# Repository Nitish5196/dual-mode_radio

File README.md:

<h1>DUAL_MODE_RADIO-DMR </h1>
DMR(DUAL MODE RADIO) is a small portable radio that combines two different things in one device:<ul>
<li>AIRLINK is a small portable radio that combines two different things in one device:</li>
<li>VHF amateur radio for two-way communication</li></ul><br>
The controller is an ESP32. It controls the display, buttons, rotary encoder and the radio module<br>
<h3> Main Components</h3>

- ESP32 DevKitC – main controller
- SA828-VHF – VHF transceiver
- RDA5807M – FM receiver
- PAM8403 – audio amplifier
- OLED – displays frequency and status
- Rotary Encoder – tuning and navigation
- TP4056 – battery charging
- Boost Converter – provides 5V power
- 3.3V Regulator – provides 3.3V power
- 18650 – rechargeable battery
- SMA Connector – VHF antenna connection
- Speakers – audio output
<h2>BOM:</h2>
<ul>
<li>Custom PCB ×1</li>
<li>ESP32 DevKitC ×1</li>
<li>SA828-VHF ×1</li>
<li>RDA5807M FM Module ×1</li>
<li>PAM8403 Amplifier Module ×1</li>
<li>0.96" OLED Display ×1</li>
<li>Rotary Encoder ×1</li>
<li>Push Buttons ×3</li>
<li>ON/OFF Switch ×1</li>
<li>RK097G B100K Potentiometer ×1</li>
<li>SMA Connector ×1</li>
<li>TP4056 Charger ×1</li>
<li>5V Boost Converter ×1</li>
<li>3.3V Regulator ×1</li>
<li>18650 Battery ×1</li>
<li>8Ω Speakers ×3</li>
<li>2.54mm Headers/Connectors ×1 set</li>
<li>3D Printed Case ×1</li>
<li>Breadboard ×1</li>
<li>Male-to-Male Jumper Wires ×1 set</li>
<li>Male-to-Female Jumper Wires ×1 set</li>
<li>Female-to-Female Jumper Wires ×1 set</li>
</ul>
<h2>PCB:</h2>

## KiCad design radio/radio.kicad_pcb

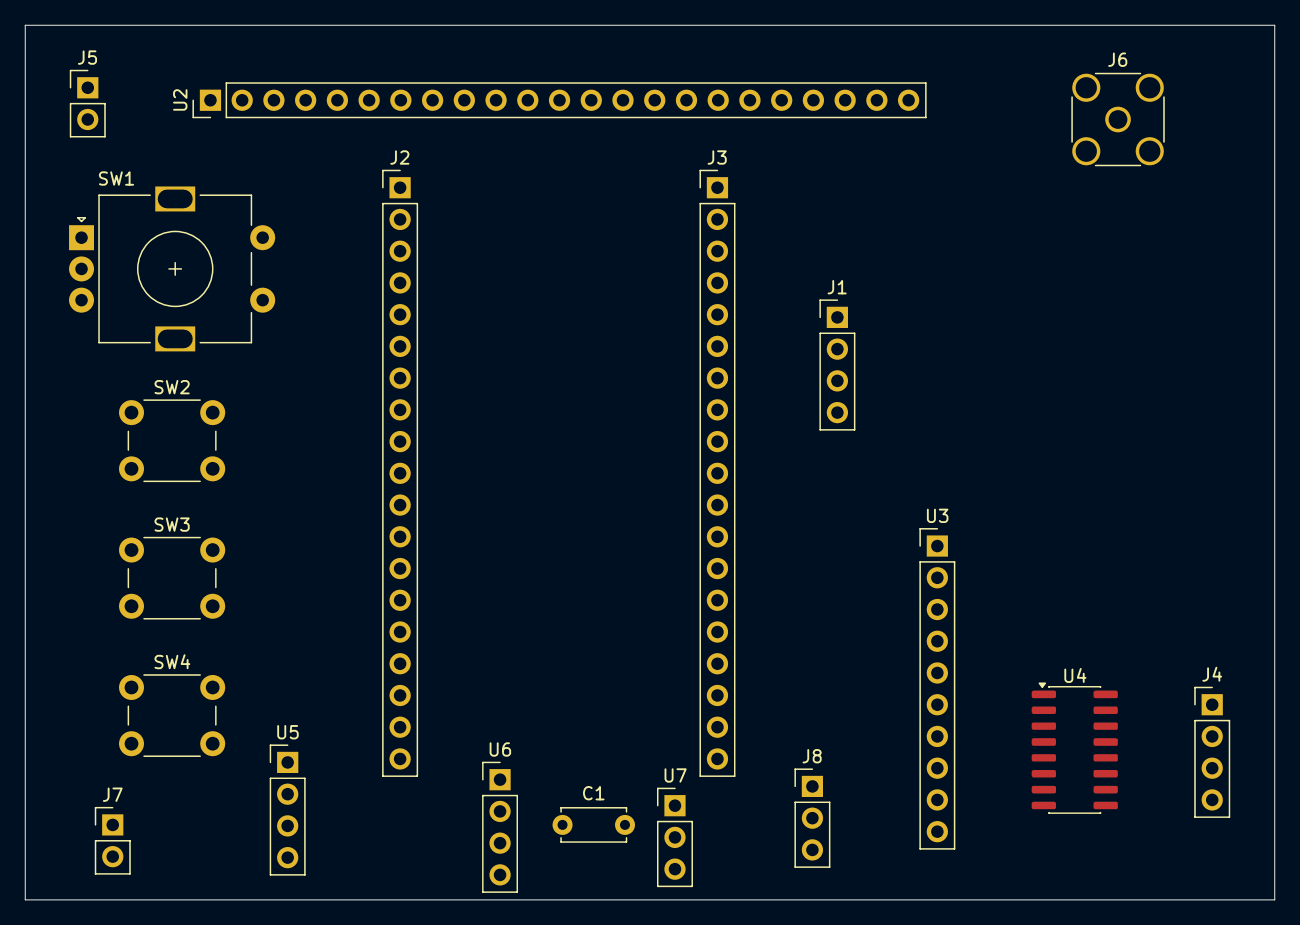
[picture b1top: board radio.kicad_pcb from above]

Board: 2 copper layers, 100.0 x 70.0 mm, 19 parts (0 on the bottom side), 26 nets, no tracks yet.

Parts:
C1: 100nF; C_Disc_D5.0mm_W2.5mm_P5.00mm
J1: Conn_01x04; PinHeader_1x04_P2.54mm_Vertical
J2: ESP32_LEFT; PinHeader_1x19_P2.54mm_Vertical
J3: ESP32_RIGHT; PinHeader_1x19_P2.54mm_Vertical
J4: FM_SPEAKERS; PinHeader_1x04_P2.54mm_Vertical
J5: RADIO_MIC; PinHeader_1x02_P2.54mm_Vertical
J6: ANTENNA_VHF; SMA_Amphenol_132134_Vertical
J7: BATTERY_18650; PinHeader_1x02_P2.54mm_Vertical
J8: POWER_SWITCH; PinHeader_1x03_P2.54mm_Vertical
SW1: ROTARY_ENCODER; RotaryEncoder_Alps_EC11E-Switch_Vertical_H20mm
SW2, SW3, SW4: SW_Push; SW_PUSH_6mm
U2: SA828-VHF; PinHeader_1x23_P2.54mm_Vertical
U3: RDA5807M-FM; PinHeader_1x10_P2.54mm_Vertical
U4: PAM8403-FM-AMP; SOIC-16_3.9x9.9mm_P1.27mm
U5: TP4056_CHARGER; PinHeader_1x04_P2.54mm_Vertical
U6: 5V_BOOST; PinHeader_1x04_P2.54mm_Vertical
U7: 3V3_REGULATOR; PinHeader_1x03_P2.54mm_Vertical

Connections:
+3V3: J1.1, J2.1, J3.1, U2.3, U2.4, U3.5, U7.3
+5V: U2.22, U4.4 (PVDD), U4.5 (~MUTE), U4.6 (VDD), U4.12 (~SHDN), U4.13 (PVDD), U6.3, U7.1
/BACK_BTN: J2.6, SW3.1
/BAT+: J7.1, J8.1, U5.3, U6.1
/ENC_A: J2.7, SW1.A
/ENC_B: J2.8, SW1.B
/ENC_SW: J2.5, SW1.S1
/FM_AUDIO_L: U3.8, U4.7 (INL)
/FM_AUDIO_R: U3.7, U4.10 (INR)
/FM_L+: J4.1, U4.1 (LOUT+)
/FM_L-: J4.2, U4.3 (LOUT-)
/FM_R+: J4.3, U4.16 (ROUT+)
/FM_R-: J4.4, U4.14 (ROUT-)
/MENU_BTN: J2.3, SW2.1
/MIC+: J5.1, U2.1
/MIC-: J5.2, U2.2
/OLED_SCL: J1.4, J3.4, U3.2
/OLED_SDA: J1.3, J3.3, U3.1
/RADIO_CS: J2.10, U2.23
/RADIO_PTT: J2.9, SW4.1, U2.20
/RADIO_RX: J3.12, U2.18
/RADIO_SPKEN: J2.11, U2.9
/RADIO_TX: J3.11, U2.19
/VHF_ANT: J6.1 (In), U2.12
GND: C1.2, J1.2, J2.14, J3.2, J6.2 (Ext), J7.2, J8.3, SW1.C, SW1.S2, SW2.2, SW3.2, SW4.2, U2.5, U2.6, U2.7, U2.10, U2.11, U2.13, U2.21, U3.3, U3.6, U3.9, U4.2 (PGND), U4.11 (GND), U4.15 (PGND), U5.2, U5.4, U6.2, U6.4, U7.2
unnamed: C1.1, U4.8 (VREF)

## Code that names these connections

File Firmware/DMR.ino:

#include <Wire.h>
#include <Adafruit_GFX.h>
#include <Adafruit_SSD1306.h>

#define SCREEN_WIDTH 128
#define SCREEN_HEIGHT 64
#define OLED_ADDR 0x3C
Adafruit_SSD1306 display(SCREEN_WIDTH, SCREEN_HEIGHT, &Wire, -1);


#define ENCODER_CLK    14
#define ENCODER_DT     27
#define ENCODER_SW     26
#define MENU_BTN       25
#define BACK_BTN       33
#define PTT_BTN        32
#define OLED_SDA       21
#define OLED_SCL       22

enum Screen {
  BOOT,
  MAIN_MENU,
  FM_RADIO,
  VHF_RADIO,
  SETTINGS,
  FM_SETTINGS,
  ABOUT
};

Screen currentScreen = BOOT;
Screen previousScreen = MAIN_MENU;
unsigned long bootTime = 0;

int menuSelection = 0;
float fmFreq = 98.3f;
float vhfFreq = 145.5f;
int vhfChannel = 1;
bool vhfTX = false;
int settingsSelection = 0;

volatile int encoderPos = 0;
volatile bool encoderPressed = false;

void IRAM_ATTR encoderInterrupt() {
  if (digitalRead(ENCODER_CLK) == digitalRead(ENCODER_DT)) {
    encoderPos++;
  } else {
    encoderPos--;
  }
}

void IRAM_ATTR encoderClick() {
  encoderPressed = true;
}

void setup() {
  Serial.begin(115200);
  
  pinMode(ENCODER_CLK, INPUT_PULLUP);
  pinMode(ENCODER_DT, INPUT_PULLUP);
  pinMode(ENCODER_SW, INPUT_PULLUP);
  pinMode(MENU_BTN, INPUT_PULLUP);
  pinMode(BACK_BTN, INPUT_PULLUP);
  pinMode(PTT_BTN, INPUT_PULLUP);
  
  attachInterrupt(digitalPinToInterrupt(ENCODER_CLK), encoderInterrupt, CHANGE);
  attachInterrupt(digitalPinToInterrupt(ENCODER_SW), encoderClick, FALLING);
  
  if (!display.begin(SSD1306_SWITCHCAPVCC, OLED_ADDR)) {
    Serial.println("OLED init failed");
    while (1);
  }
  
  display.setTextSize(1);
  display.setTextColor(SSD1306_WHITE);
  display.clearDisplay();
  
  currentScreen = BOOT;
  bootTime = millis();
}

void loop() {
  handleInputs();
  updateScreen();
  delay(50);
}

void handleInputs() {
  static int lastEncoderPos = 0;
  
  if (encoderPos != lastEncoderPos) {
    int delta = encoderPos - lastEncoderPos;
    lastEncoderPos = encoderPos;
    handleEncoderRotation(delta);
  }
  
  if (encoderPressed) {
    encoderPressed = false;
    handleEncoderPress();
    delay(200);
  }
  
  if (!digitalRead(MENU_BTN)) {
    handleMenuButton();
    delay(200);
  }
  
  if (!digitalRead(BACK_BTN)) {
    handleBackButton();
    delay(200);
  }
  
  if (!digitalRead(PTT_BTN)) {
    vhfTX = true;
  } else {
    vhfTX = false;
  }
}

void handleEncoderRotation(int delta) {
  switch (currentScreen) {
    case MAIN_MENU:
      menuSelection = constrain(menuSelection + delta, 0, 2);
      break;
    case FM_RADIO:
      fmFreq = constrain(fmFreq + (delta * 0.1f), 87.5f, 108.0f);
      break;
    case VHF_RADIO:
      vhfFreq = constrain(vhfFreq + (delta * 0.025f), 136.0f, 174.0f);
      break;
    case SETTINGS:
      settingsSelection = constrain(settingsSelection + delta, 0, 3);
      break;
  }
}

void handleEncoderPress() {
  switch (currentScreen) {
    case MAIN_MENU:
      if (menuSelection == 0) currentScreen = FM_RADIO;
      else if (menuSelection == 1) currentScreen = VHF_RADIO;
      else if (menuSelection == 2) currentScreen = SETTINGS;
      break;
    case SETTINGS:
      if (settingsSelection == 3) currentScreen = ABOUT;
      break;
  }
}

void handleMenuButton() {
  if (currentScreen == FM_RADIO) {
    previousScreen = FM_RADIO;
    currentScreen = FM_SETTINGS;
  }
}

void handleBackButton() {
  if (currentScreen == MAIN_MENU) return;
  
  if (currentScreen == FM_SETTINGS) {
    currentScreen = previousScreen;
  } else if (currentScreen == ABOUT) {
    currentScreen = SETTINGS;
  } else {
    currentScreen = MAIN_MENU;
  }
  menuSelection = 0;
  settingsSelection = 0;
}

void updateScreen() {
  display.clearDisplay();
  
  switch (currentScreen) {
    case BOOT:
      drawBoot();
      break;
    case MAIN_MENU:
      drawMainMenu();
      break;
    case FM_RADIO:
      drawFMRadio();
      break;
    case VHF_RADIO:
      drawVHFRadio();
      break;
    case SETTINGS:
      drawSettings();
      break;
    case FM_SETTINGS:
      drawFMSettings();
      break;
    case ABOUT:
      drawAbout();
      break;
  }
  
  display.display();
}

void drawBoot() {
  if (millis() - bootTime > 2000) {
    currentScreen = MAIN_MENU;
    return;
  }
  
  display.setTextSize(2);
  display.setCursor(25, 16);
  display.println("DMR");
  
  display.setTextSize(1);
  display.setCursor(10, 40);
  display.println("Dual Mode Radio");
}

void drawMainMenu() {
  display.setTextSize(1);
  display.setCursor(0, 0);
  display.println("DMR");
  
  display.setCursor(0, 16);
  if (menuSelection == 0) display.print("> ");
  else display.print("  ");
  display.println("FM RADIO");
  
  display.setCursor(0, 24);
  if (menuSelection == 1) display.print("> ");
  else display.print("  ");
  display.println("VHF RADIO");
  
  display.setCursor(0, 32);
  if (menuSelection == 2) display.print("> ");
  else display.print("  ");
  display.println("SETTINGS");
}

void drawFMRadio() {
  display.setTextSize(1);
  display.setCursor(0, 0);
  display.println("FM RADIO");
  
  display.setTextSize(2);
  display.setCursor(20, 24);
  display.print(fmFreq, 2);
  display.println(" MHz");
  
  display.setTextSize(1);
  display.setCursor(40, 50);
  display.println("STEREO");
}

void drawVHFRadio() {
  display.setTextSize(1);
  display.setCursor(0, 0);
  display.println("VHF RADIO");
  
  display.setTextSize(2);
  display.setCursor(10, 24);
  display.print(vhfFreq, 3);
  display.println(" MHz");
  
  display.setTextSize(1);
  display.setCursor(40, 50);
  if (vhfTX) display.println("TX");
  else display.println("RX");
  
  display.setCursor(90, 50);
  display.print("CH ");
  display.println(vhfChannel);
}

void drawSettings() {
  display.setTextSize(1);
  display.setCursor(0, 0);
  display.println("SETTINGS");
  
  display.setCursor(0, 16);
  if (settingsSelection == 0) display.print("> ");
  else display.print("  ");
  display.println("FM STEP");
  
  display.setCursor(0, 24);
  if (settingsSelection == 1) display.print("> ");
  else display.print("  ");
  display.println("DISPLAY");
  
  display.setCursor(0, 32);
  if (settingsSelection == 2) display.print("> ");
  else display.print("  ");
  display.println("BATTERY");
  
  display.setCursor(0, 40);
  if (settingsSelection == 3) display.print("> ");
  else display.print("  ");
  display.println("ABOUT");
}

void drawFMSettings() {
  display.setTextSize(1);
  display.setCursor(0, 0);
  display.println("FM OPTIONS");
  
  display.setCursor(0, 20);
  display.println("RDS: OFF");
  display.setCursor(0, 30);
  display.println("VOL: 8");
  display.setCursor(0, 40);
  display.println("MUTE: OFF");
}

void drawAbout() {
  display.setTextSize(1);
  display.setCursor(20, 10);
  display.println("DMR");
  
  display.setCursor(5, 24);
  display.println("Dual Mode Radio");
  
  display.setCursor(0, 38);
  display.println("ESP32 + SA828 + FM");
  
  display.setCursor(50, 50);
  display.println("v1.0");
}
